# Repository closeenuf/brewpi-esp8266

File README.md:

# brewpi-esp8266
A fork of the brewpi-esp8266 project by thorrak (https://github.com/thorrak/brewpi-esp8266), with some modifications to the pinouts to suit my specific setup.

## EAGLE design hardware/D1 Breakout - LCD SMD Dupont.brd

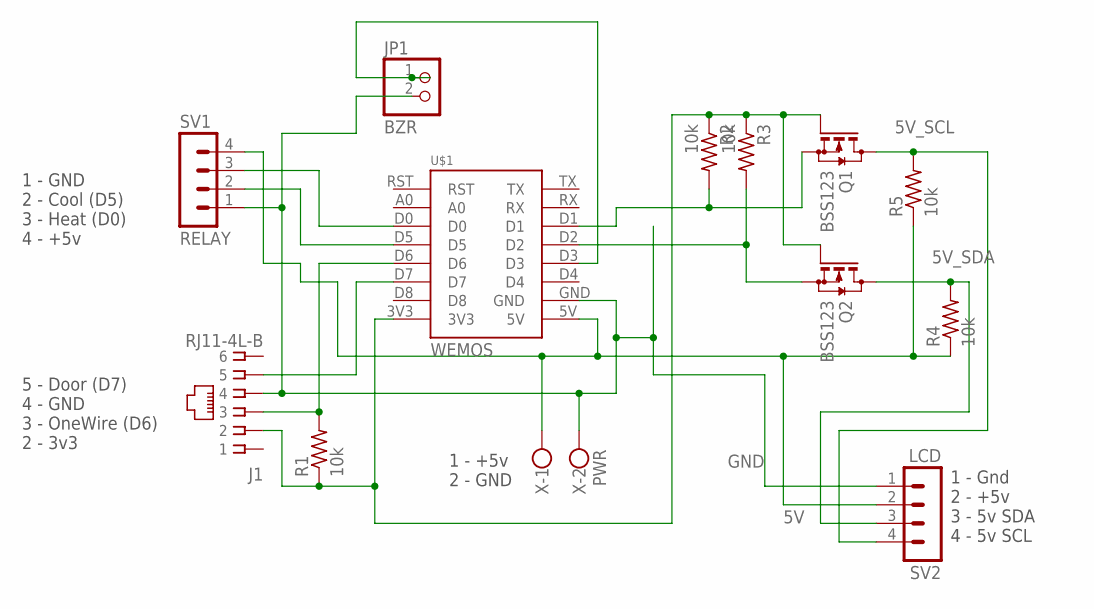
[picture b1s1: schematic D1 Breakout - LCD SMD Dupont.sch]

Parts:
J1: RJ11-4L-B; RJ11-NO_SHIELD
JP1: BZR; 1X02
Q1, Q2: BSS123; SOT23
R1, R2, R3, R4, R5: 10k; R0805
SV1: RELAY; MA04-1
SV2: LCD; MA04-1
U$1: WEMOS
X: PWR; W237-102

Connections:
3V3_SCL: Q1.2 (S), R2.2, U$1.D1
3V3_SDA: Q2.2 (S), R3.2, U$1.D2
5V: R4.1, R5.1, SV1.4, SV2.2, U$1.5V, X.1
5V_SCL: Q1.3 (D), R5.2, SV2.4
5V_SDA: Q2.3 (D), R4.2, SV2.3
D6: J1.3, R1.2, U$1.D6
D7: J1.5, U$1.D7
GND: J1.4, JP1.2, SV1.1, SV2.1, U$1.GND, X.2
unnamed: J1.2, Q1.1 (G), Q2.1 (G), R1.1, R2.1, R3.1, U$1.3V3
unnamed: JP1.1, U$1.D3
unnamed: SV1.2, U$1.D5
unnamed: SV1.3, U$1.D0

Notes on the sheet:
1 - GND 2 - Cool (D5) 3 - Heat (D0) 4 - +5v
5 - Door (D7) 4 - GND 3 - OneWire (D6) 2 - 3v3
1 - +5v 2 - GND
1 - Gnd 2 - +5v 3 - 5v SDA 4 - 5v SCL

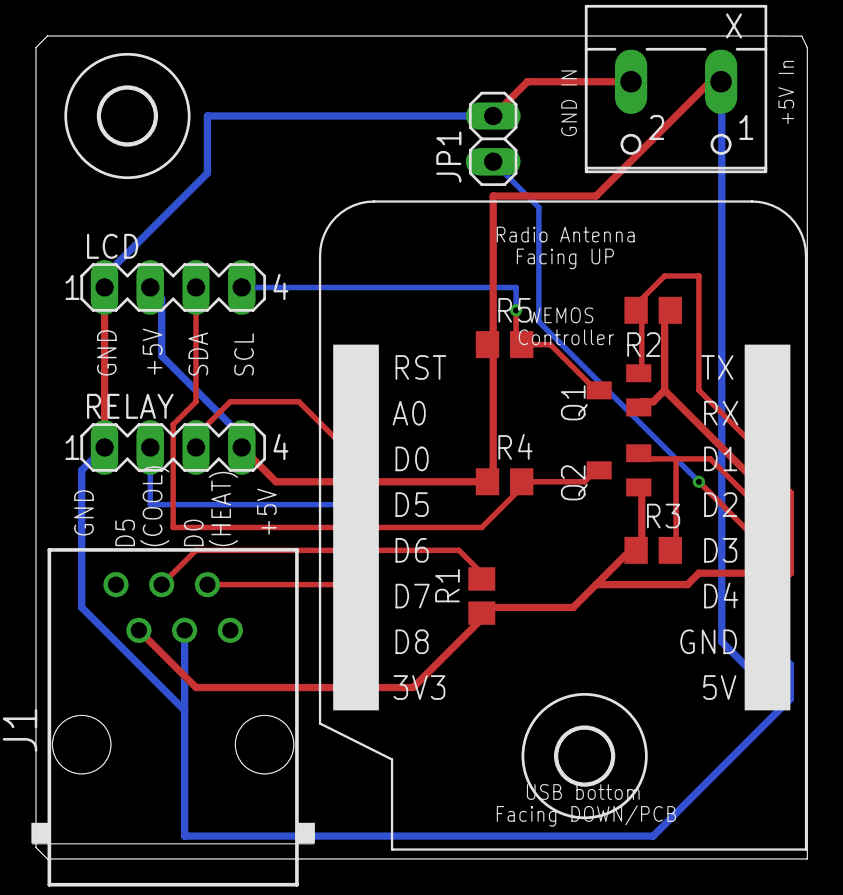
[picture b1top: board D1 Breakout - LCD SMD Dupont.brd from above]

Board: 2 copper layers, 42.8 x 45.7 mm, 15 parts (0 on the bottom side), 12 nets.

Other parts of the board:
U$2, U$4: 3,0

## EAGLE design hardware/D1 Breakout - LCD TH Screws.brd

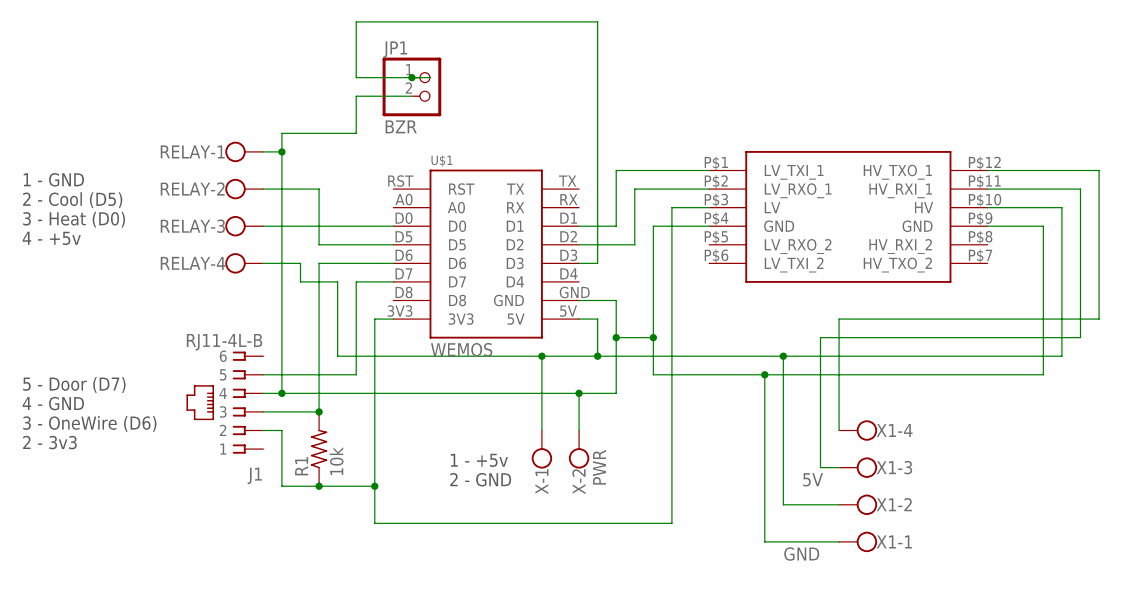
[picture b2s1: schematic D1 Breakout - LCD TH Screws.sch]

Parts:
J1: RJ11-4L-B; RJ11-NO_SHIELD
JP1: BZR; 1X02
R1: 10k; 0207/5V
RELAY: W237-4
U$1: WEMOS
U$3: LOGIC_LEVEL_CONVERTER
X: PWR; W237-102
X1: W237-4

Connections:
5V: RELAY.4, U$1.5V, U$3.P$10 (HV), X.1, X1.2
D0: RELAY.3, U$1.D0
D5: RELAY.2, U$1.D5
D6: J1.3, R1.2, U$1.D6
D7: J1.5, U$1.D7
GND: J1.4, JP1.2, RELAY.1, U$1.GND, U$3.P$4 (GND), U$3.P$9 (GND), X.2, X1.1
unnamed: U$1.D1, U$3.P$1 (LV_TXI_1)
unnamed: U$1.D2, U$3.P$2 (LV_RXO_1)
unnamed: J1.2, R1.1, U$1.3V3, U$3.P$3 (LV)
unnamed: U$3.P$12 (HV_TXO_1), X1.4
unnamed: U$3.P$11 (HV_RXI_1), X1.3
unnamed: JP1.1, U$1.D3

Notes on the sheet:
1 - GND 2 - Cool (D5) 3 - Heat (D0) 4 - +5v
5 - Door (D7) 4 - GND 3 - OneWire (D6) 2 - 3v3
1 - +5v 2 - GND

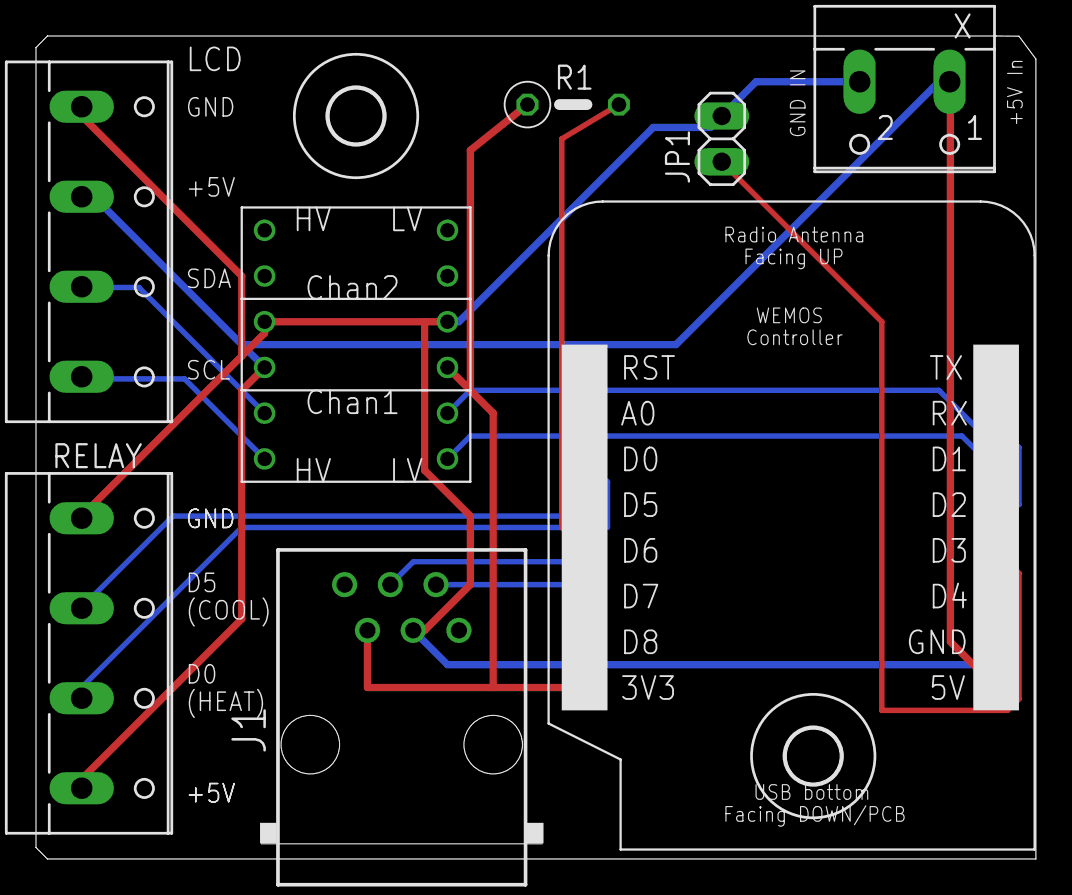
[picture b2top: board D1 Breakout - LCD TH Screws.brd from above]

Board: 2 copper layers, 55.5 x 45.7 mm, 10 parts (0 on the bottom side), 12 nets.

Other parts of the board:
U$2, U$4: 3,0

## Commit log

2018-04-01 changes to pinout for feather HUZZAH esp8266 board
2018-08-17 migration to vscode
2019-12-28 Removed files from repo not to be tracked
2019-12-28 Disable LCD and building serial firmware

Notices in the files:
parts and their libraries:
SparkFun-Boards: Licensing: Creative Commons ShareAlike 4.0 International - https://creativecommons.org/licenses/by-sa/4.0
